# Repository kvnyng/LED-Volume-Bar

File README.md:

# LED-Volume-Bar
Here are the design files for my LED Volume Bar project (Project page at http://bykevinyang.com/LED-Volume-Bar)

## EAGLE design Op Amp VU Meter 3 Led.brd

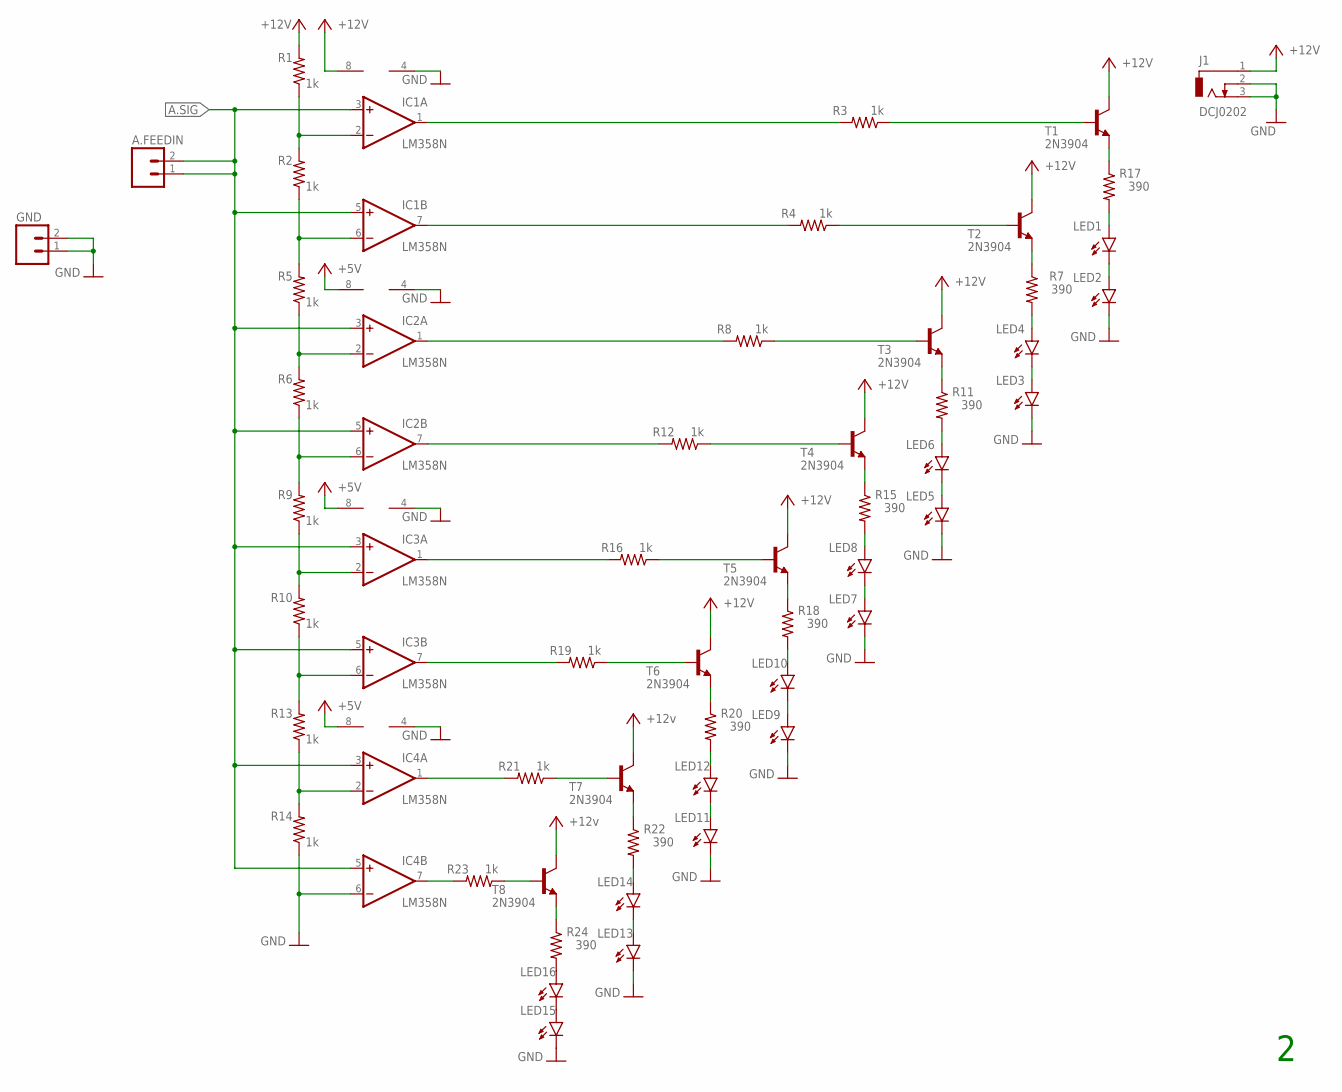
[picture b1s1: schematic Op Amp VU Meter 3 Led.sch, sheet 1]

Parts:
A.FEEDIN: MA02; 02PA
GND: MA02; 02PA
IC1, IC2, IC3, IC4: LM358N; DIL08
J1: DCJ0202
LED1, LED2, LED3, LED4, LED5, LED6, LED7, LED8, LED9, LED10, LED11, LED12, LED13, LED14, LED15, LED16: LED5MM
R1, R2, R3, R4, R5, R6, R8, R9, R10, R12, R13, R14, R16, R19, R21, R23: 1k; 0207/12
R7, R11, R15, R17, R18, R20, R22, R24: 390; 0207/12
T1, T2, T3, T4, T5, T6, T7, T8: 2N3904; TO92

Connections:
+5V: IC1.8 (V+), IC2.8 (V+), IC3.8 (V+), IC4.8 (V+), J1.1, R1.2, T1.1 (C), T2.1 (C), T3.1 (C), T4.1 (C), T5.1 (C), T6.1 (C), T7.1 (C), T8.1 (C); also elsewhere on the board
A.SIG: A.FEEDIN.1, A.FEEDIN.2, IC1.3 (+IN), IC1.5 (+IN), IC2.3 (+IN), IC2.5 (+IN), IC3.3 (+IN), IC3.5 (+IN), IC4.3 (+IN), IC4.5 (+IN); also elsewhere on the board
GND: GND.1, GND.2, IC1.4 (V-), IC2.4 (V-), IC3.4 (V-), IC4.4 (V-), IC4.6 (-IN), J1.2, J1.3, LED2.K (C), LED3.K (C), LED5.K (C), LED7.K (C), LED9.K (C), LED11.K (C), LED13.K (C), LED15.K (C), R14.1; also elsewhere on the board
unnamed: IC1.2 (-IN), R1.1, R2.2
unnamed: IC1.6 (-IN), R2.1, R5.2
unnamed: IC1.1 (OUT), R3.2
unnamed: R3.1, T1.2 (B)
unnamed: IC1.7 (OUT), R4.2
unnamed: LED1.K (C), LED2.A
unnamed: IC2.2 (-IN), R5.1, R6.2
unnamed: IC2.6 (-IN), R6.1, R9.2
unnamed: IC2.1 (OUT), R8.2
unnamed: LED1.A, R17.2
unnamed: IC2.7 (OUT), R12.2
unnamed: R8.1, T3.2 (B)
unnamed: IC3.6 (-IN), R10.1, R13.2
unnamed: IC3.2 (-IN), R9.1, R10.2
unnamed: IC3.1 (OUT), R16.2
unnamed: R4.1, T2.2 (B)
unnamed: IC3.7 (OUT), R19.2
unnamed: R7.1, T2.3 (E)
unnamed: IC4.2 (-IN), R13.1, R14.2
unnamed: IC4.1 (OUT), R21.2
unnamed: LED3.A, LED4.K (C)
unnamed: IC4.7 (OUT), R23.2
unnamed: LED4.A, R7.2
unnamed: R17.1, T1.3 (E)
unnamed: R11.1, T3.3 (E)
unnamed: LED5.A, LED6.K (C)
unnamed: LED6.A, R11.2
unnamed: R12.1, T4.2 (B)
unnamed: R15.1, T4.3 (E)
unnamed: LED7.A, LED8.K (C)
unnamed: LED8.A, R15.2
unnamed: R16.1, T5.2 (B)
unnamed: R18.1, T5.3 (E)
unnamed: LED9.A, LED10.K (C)
unnamed: LED10.A, R18.2
unnamed: R19.1, T6.2 (B)
unnamed: R20.1, T6.3 (E)
unnamed: LED11.A, LED12.K (C)
unnamed: LED12.A, R20.2
unnamed: R21.1, T7.2 (B)
unnamed: R22.1, T7.3 (E)
unnamed: LED13.A, LED14.K (C)
unnamed: LED14.A, R22.2
unnamed: R23.1, T8.2 (B)
unnamed: R24.1, T8.3 (E)
unnamed: LED15.A, LED16.K (C)
unnamed: LED16.A, R24.2

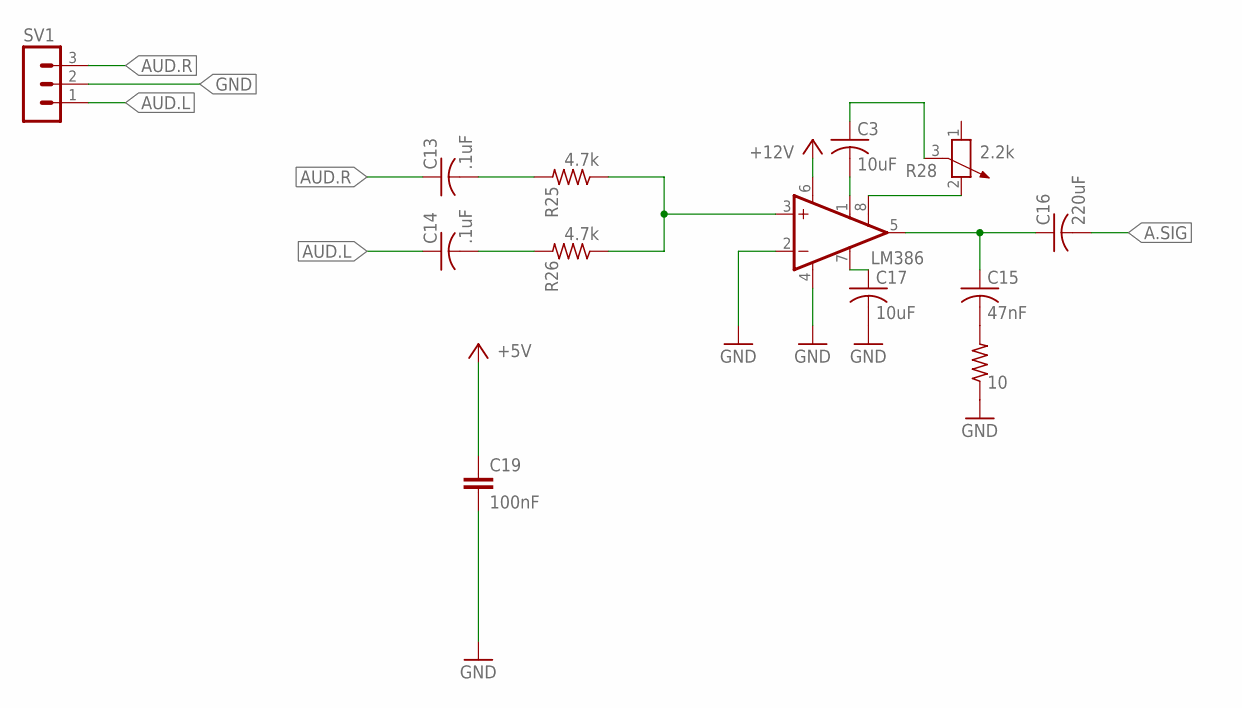
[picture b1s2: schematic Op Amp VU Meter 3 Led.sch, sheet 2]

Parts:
C3, C17: 10uF; C050-024X044
C13, C14: .1uF; C050-024X044
C15: 47nF; C050-024X044
C16: 220uF; C050-024X044
C19: 100nF; C025-025X050
LM386: LM386N-1; DIL08
R25, R26: 4.7k; 0207/12
R27: 10; 0207/12
R28: 2.2k; PT-10S
SV1: MA03-1

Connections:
+5V: C19.1, LM386.6 (VS); also elsewhere on the board
A.SIG: C16.2; also elsewhere on the board
AUD.L: C14.1, SV1.1
AUD.R: C13.1, SV1.3
GND: C17.2, C19.2, LM386.2 (-IN), LM386.4 (GND), R27.1, SV1.2; also elsewhere on the board
unnamed: C13.2, R25.2
unnamed: C14.2, R26.2
unnamed: LM386.3 (+IN), R25.1, R26.1
unnamed: C15.1, C16.1, LM386.5 (OUT)
unnamed: C17.1, LM386.7 (BYPASS)
unnamed: C15.2, R27.2
unnamed: C3.2, LM386.1 (GAIN)
unnamed: LM386.8 (GAIN), R28.2
unnamed: C3.1, R28.3

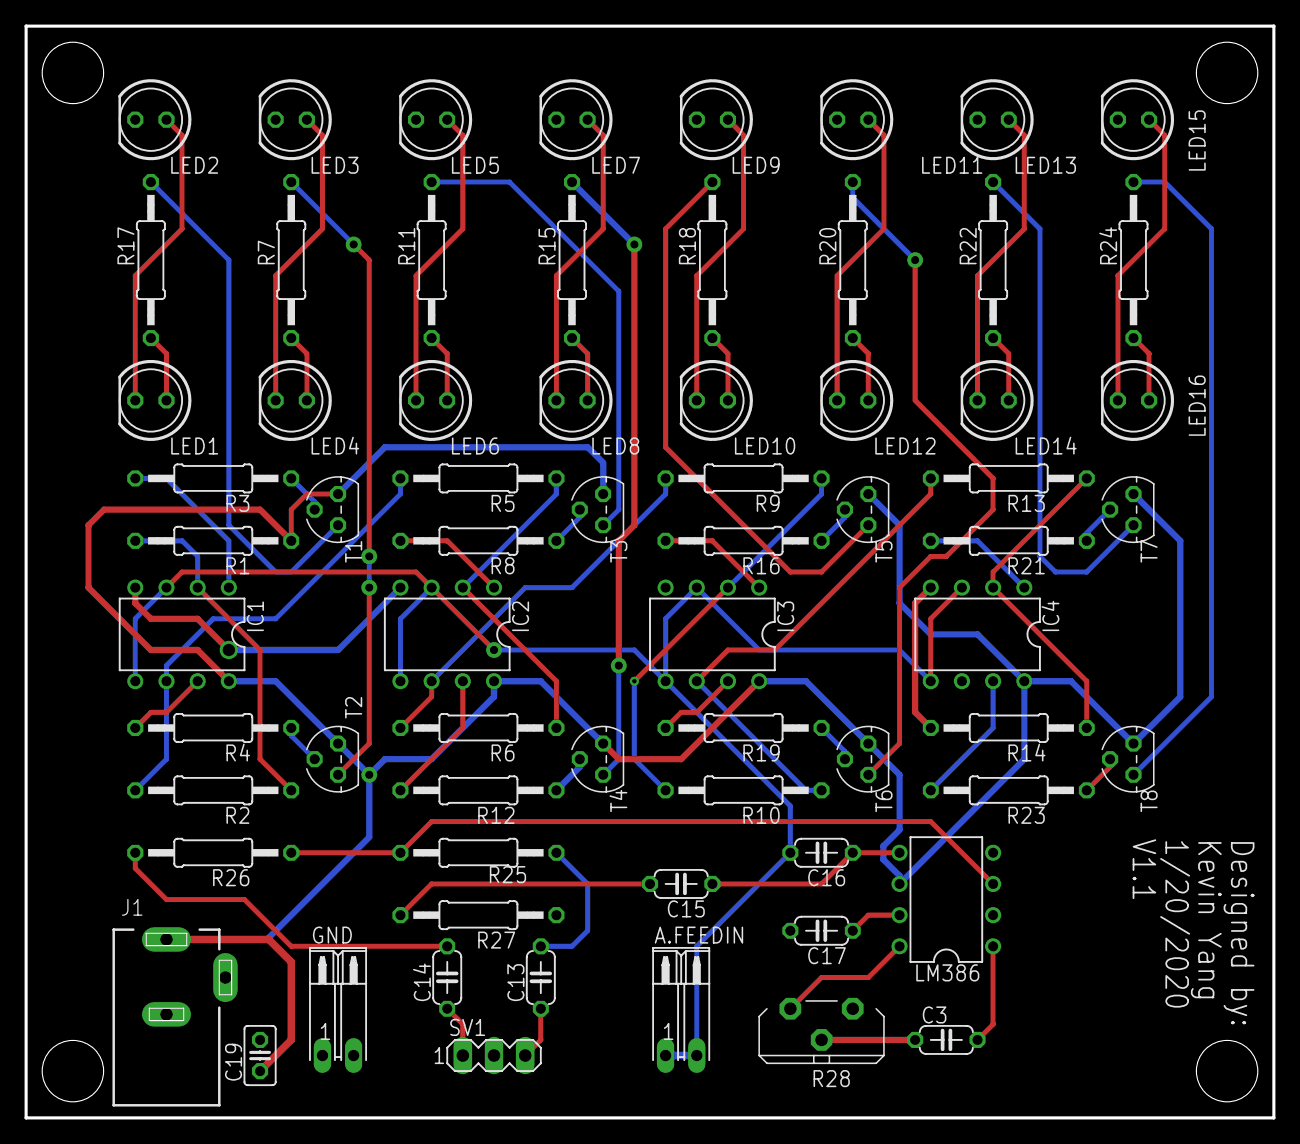
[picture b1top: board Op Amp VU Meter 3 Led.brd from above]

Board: 2 copper layers, 101.6 x 88.9 mm, 68 parts (0 on the bottom side), 61 nets.

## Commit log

2020-03-11 Added Gerber files
2020-03-11 Added Gerber files
    You need both the assembly files and Gerber files to make the PCB. The assembly files are to simply cut the mounting holes on the PCB.
2020-03-14 Added case
2020-03-14 Added Gerber Files
    Assembly files are needed for PCB production. They are the directions for CNC cutting in the PCB's holes
2020-03-14 Added schematics
2020-03-14 Added PCB
